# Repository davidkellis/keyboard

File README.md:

# TKL Low-Profile Bluetooth Keyboard (Project Notes)

## Decisions so far
- Layout: ANSI TKL (87-key).
- Switches: Kailh Deep Sea Silent Mini Low-Profile (Kailh page indicates Choc v2 family / PG1353).
- Footprint target: Choc v2 (not Cherry MX pin layout, not Choc v1 keycaps).
- Stem: MX-style "+" stem (per Choc v2 description).
- Hot-swap: required.
- Switch footprints: MX_V2 Kailh PG1353 hotswap library (Kailh_PG1353_Hotswap).
- Controller: nice!nano v2-compatible BLE clones (same pinout as nice!nano v2).
- Features: no rotary encoder, no OLED; white backlight via edge-lit plate.
- Case: custom, as thin as possible.
- Firmware: ZMK.
- Fn layer: right Menu key.
- Device switching: map Device 1/2/3 to the three keys right of F12 (Print/Scroll/Pause positions).
- Keymap change: Insert key performs Print Screen.
- Re-pair: Fn+Device 1/2/3 macros force-select profile 0/1/2, clear bond (BT_CLR), then re-select that profile to enter pairing; avoids BT_CLR_ALL. Order: BT_SEL N -> BT_CLR -> BT_SEL N.
- Device select: tap Device 1/2/3 selects and connects to profile 0/1/2.
- Battery: 4 mm thickness, JST-PH.
- Keycaps: low-profile, 8–9 mm height.
- Stabilizers: Kailh Choc low-profile plate-mount (4x 2u, 1x 6.25u).
- Backlight: single-zone white; use 1 mm clear plate as the edge-lit light guide with up to 16 side-emitting 1206 LEDs around the perimeter; warm/neutral based on LED availability.
- External power switch: yes, edge-mounted slide switch on the back edge (back-right).
- Reset/boot access: onboard only.
- Matrix: 8x16; rows on nice!nano (D4-D9, D16, D14) and columns on MCP23017.
- MCP23017 I2C address: 0x20 (A0-A2 tied to GND).
- PCB thickness: 1.2 mm (initial assumption for thin build).
- KiCad libraries: ScottoKicad vendored at kicad/lib/ScottoKicad.

## Findings / constraints
- Kailh product note: these switches are not compatible with Cherry MX key pin layouts and not compatible with Choc v1 keycaps.
- Beekeeb Choc v2 page: Choc v2 uses the same hot-swap sockets as Choc v1.
- Thin build drivers: battery thickness, PCB thickness, and component height will dominate overall thickness.

## Open decisions
- Warm vs neutral LED selection based on availability.
- LED part selection based on availability (side-emitting 1206, warm/neutral).
- Side-emitting LED footprint (current schematic uses generic 1206 placeholder).

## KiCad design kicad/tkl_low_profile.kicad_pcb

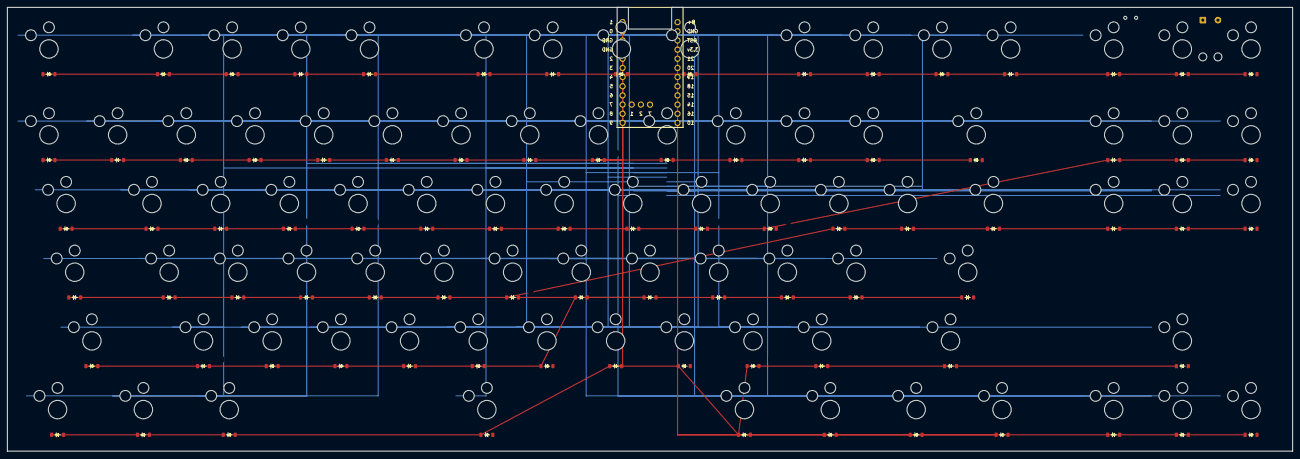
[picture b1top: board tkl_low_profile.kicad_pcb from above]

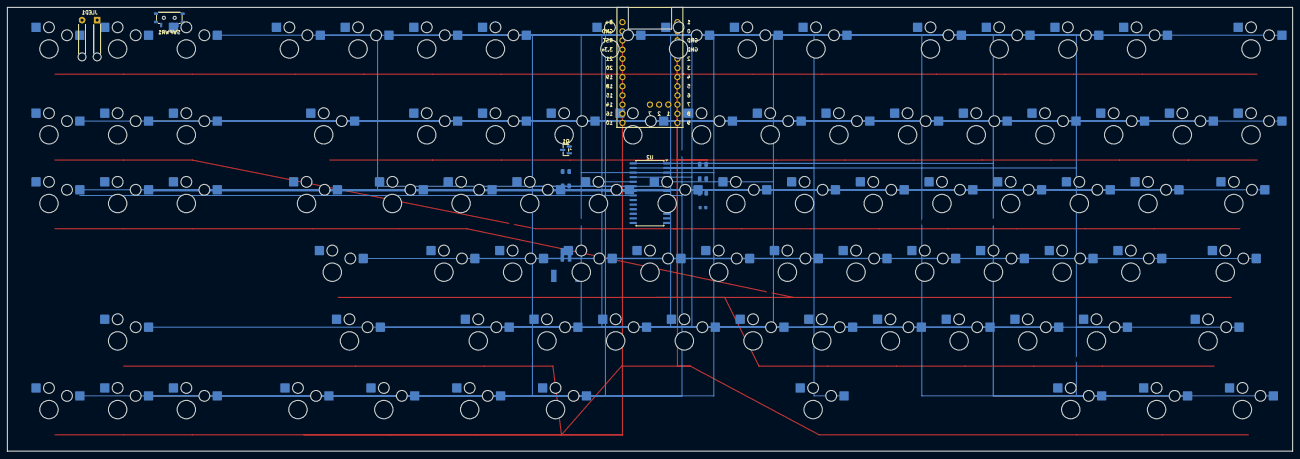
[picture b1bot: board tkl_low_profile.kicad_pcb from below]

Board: 2 copper layers, 356.4 x 123.1 mm, 186 parts (99 on the bottom side), 121 nets.

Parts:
C1: 0.1u; Capacitor_0603
D1, D2, D3, D4, D5, D6, D7, D8, D9, D10, D11, D12, D13, D14, D15, D16, D17, D18, D19, D20, D21, D22, D23, D24, D25, D26, D27, D28, D29, D30, D31, D32, D33, D34, D35, D36, D37, D38, D39, D40, D41, D42, D43, D44, D45, D46, D47, D48, D49, D50, D51, D52, D53, D54, D55, D56, D57, D58, D59, D60, D61, D62, D63, D64, D65, D66, D67, D68, D69, D70, D71, D72, D73, D74, D75, D76, D77, D78, D79, D80, D81, D82, D83, D84, D85, D86, D87: D; Diode_SOD-123
JBAT1: JST-PH; Connector_1x02_JST-PH
JLED1: LED_HARNESS; SolderWire-0.25sqmm_1x02_P4.2mm_D0.65mm_OD1.7mm_Relief
Q1: NMOS; SOT-23
R1, R2: 4.7k; Resistor_0805
R3: 10k; Resistor_0805
R4: 100; Resistor_0805
R5: 100k; Resistor_0805
SW1, SW2, SW3, SW4, SW5, SW6, SW7, SW8, SW9, SW10, SW11, SW12, SW13, SW14, SW15, SW16, SW17, SW18, SW19, SW20, SW21, SW22, SW23, SW24, SW25, SW26, SW27, SW28, SW29, SW31, SW32, SW33, SW35, SW36, SW37, SW38, SW39, SW40, SW41, SW42, SW43, SW44, SW45, SW46, SW48, SW49, SW50, SW52, SW53, SW54, SW55, SW56, SW57, SW58, SW59, SW60, SW61, SW62, SW65, SW66, SW67, SW68, SW69, SW70, SW71, SW72, SW73, SW74, SW76, SW85, SW86, SW87: SW_Push; Kailh-PG1353-Hotswap-1U
SW30: SW_Push; Kailh-PG1353-Hotswap-2U
SW34, SW47: SW_Push; Kailh-PG1353-Hotswap-1.5U
SW51: SW_Push; Kailh-PG1353-Hotswap-1.75U
SW63, SW64: SW_Push; Kailh-PG1353-Hotswap-2.25U
SW75: SW_Push; Kailh-PG1353-Hotswap-2.75U
SW77, SW78, SW79, SW81, SW82, SW83, SW84: SW_Push; Kailh-PG1353-Hotswap-1.25U
SW80: SW_Push; Kailh-PG1353-Hotswap-6.25U
SWPWR1: Power_Switch; Switch_MSK12C02
U1: Nice_Nano_V2
U2: MCP23017; SOIC-28W_7.5x17.9mm_P1.27mm

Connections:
/+3V3: C1.2, JLED1.1, R1.2, R2.2, R3.2, U1.16 (15), U2.10 (VSS)
/BL_GATE: Q1.1 (G), R4.1, R5.1
/BL_NEG: JLED1.2, Q1.2 (S)
/BL_PWM: R4.2, U1.24 (B+)
/GND: C1.1, Q1.3 (D), R5.2, U1.9 (6), U1.10 (7), U1.14 (16), U2.9 (VDD), U2.12 (SCK), U2.13 (SDA)
/MCP_RESET: R3.1, U2.20 (INTA)
/SCL: R2.1, U1.7 (4), U2.16 (A1)
/SDA: R1.1, U1.8 (5), U2.15 (A0)
/VBAT: SWPWR1.2 (B), U1.13 (10)
/VBAT_RAW: JBAT1.1, SWPWR1.3 (C)
COL0: SW1.1, SW17.1, SW31.1, SW45.1, SW58.1, SW71.1, SW82.1, SW85.1, U2.8 (GPB7)
COL1: SW2.1, SW18.1, SW32.1, SW46.1, SW59.1, SW72.1, SW83.1, SW86.1, U2.7 (GPB6)
COL2: SW3.1, SW19.1, SW33.1, SW47.1, SW60.1, SW73.1, SW84.1, SW87.1, U2.6 (GPB5)
COL3: SW4.1, SW20.1, SW34.1, SW48.1, SW61.1, SW74.1, U2.5 (GPB4)
COL4: SW5.1, SW21.1, SW35.1, SW49.1, SW62.1, SW75.1, U2.4 (GPB3)
COL5: SW6.1, SW22.1, SW36.1, SW50.1, SW63.1, SW76.1, U2.3 (GPB2)
COL6: SW7.1, SW23.1, SW37.1, SW51.1, SW64.1, SW77.1, U2.2 (GPB1)
COL7: SW8.1, SW24.1, SW38.1, SW52.1, SW65.1, SW78.1, U2.1 (GPB0)
COL8: SW9.1, SW25.1, SW39.1, SW53.1, SW66.1, SW79.1, U2.28 (GPA7)
COL9: SW10.1, SW26.1, SW40.1, SW54.1, SW67.1, SW80.1, U2.27 (GPA6)
COL10: SW11.1, SW27.1, SW41.1, SW55.1, SW68.1, SW81.1, U2.26 (GPA5)
COL11: SW12.1, SW28.1, SW42.1, SW56.1, SW69.1, U2.25 (GPA4)
COL12: SW13.1, SW29.1, SW43.1, SW57.1, SW70.1, U2.24 (GPA3)
COL13: SW14.1, SW30.1, SW44.1, U2.23 (GPA2)
COL14: SW15.1, U2.22 (GPA1)
COL15: SW16.1, U2.21 (GPA0)
unnamed: D1.2 (A), SW1.2
unnamed: D2.2 (A), SW2.2
unnamed: D3.2 (A), SW3.2
unnamed: D4.2 (A), SW4.2
unnamed: D5.2 (A), SW5.2
unnamed: D6.2 (A), SW6.2
unnamed: D7.2 (A), SW7.2
unnamed: D8.2 (A), SW8.2
unnamed: D9.2 (A), SW9.2
unnamed: D10.2 (A), SW10.2
unnamed: D11.2 (A), SW11.2
unnamed: D12.2 (A), SW12.2
unnamed: D13.2 (A), SW13.2
unnamed: D14.2 (A), SW14.2
unnamed: D15.2 (A), SW15.2
unnamed: D16.2 (A), SW16.2
unnamed: D17.2 (A), SW17.2
unnamed: D18.2 (A), SW18.2
unnamed: D19.2 (A), SW19.2
unnamed: D20.2 (A), SW20.2
unnamed: D21.2 (A), SW21.2
unnamed: D22.2 (A), SW22.2
unnamed: D23.2 (A), SW23.2
unnamed: D24.2 (A), SW24.2
unnamed: D25.2 (A), SW25.2
unnamed: D26.2 (A), SW26.2
unnamed: D27.2 (A), SW27.2
unnamed: D28.2 (A), SW28.2
unnamed: D29.2 (A), SW29.2
unnamed: D30.2 (A), SW30.2
unnamed: D31.2 (A), SW31.2
unnamed: D32.2 (A), SW32.2
unnamed: D33.2 (A), SW33.2
unnamed: D34.2 (A), SW34.2
unnamed: D35.2 (A), SW35.2
unnamed: D36.2 (A), SW36.2
unnamed: D37.2 (A), SW37.2
unnamed: D38.2 (A), SW38.2
unnamed: D39.2 (A), SW39.2
unnamed: D40.2 (A), SW40.2
unnamed: D41.2 (A), SW41.2
unnamed: D42.2 (A), SW42.2
unnamed: D43.2 (A), SW43.2
unnamed: D44.2 (A), SW44.2
unnamed: D45.2 (A), SW45.2
unnamed: D46.2 (A), SW46.2
unnamed: D47.2 (A), SW47.2
unnamed: D48.2 (A), SW48.2
unnamed: D49.2 (A), SW49.2
unnamed: D50.2 (A), SW50.2
unnamed: D51.2 (A), SW51.2
unnamed: D52.2 (A), SW52.2
unnamed: D53.2 (A), SW53.2
unnamed: D54.2 (A), SW54.2
unnamed: D55.2 (A), SW55.2
unnamed: D56.2 (A), SW56.2
unnamed: D57.2 (A), SW57.2
unnamed: D58.2 (A), SW58.2
unnamed: D59.2 (A), SW59.2
unnamed: D60.2 (A), SW60.2
unnamed: D61.2 (A), SW61.2
unnamed: D62.2 (A), SW62.2
unnamed: D63.2 (A), SW63.2
unnamed: D64.2 (A), SW64.2
unnamed: D65.2 (A), SW65.2
unnamed: D66.2 (A), SW66.2
unnamed: D67.2 (A), SW67.2
unnamed: D68.2 (A), SW68.2
unnamed: D69.2 (A), SW69.2
unnamed: D70.2 (A), SW70.2
unnamed: D71.2 (A), SW71.2
unnamed: D72.2 (A), SW72.2
unnamed: D73.2 (A), SW73.2
unnamed: D74.2 (A), SW74.2
unnamed: D75.2 (A), SW75.2
unnamed: D76.2 (A), SW76.2
unnamed: D77.2 (A), SW77.2
unnamed: D78.2 (A), SW78.2
unnamed: D79.2 (A), SW79.2
unnamed: D80.2 (A), SW80.2
unnamed: D81.2 (A), SW81.2
unnamed: D82.2 (A), SW82.2
unnamed: D83.2 (A), SW83.2
unnamed: D84.2 (A), SW84.2
unnamed: D85.2 (A), SW85.2
unnamed: D86.2 (A), SW86.2
unnamed: D87.2 (A), SW87.2
ROW0: D1.1 (K), D2.1 (K), D3.1 (K), D4.1 (K), D5.1 (K), D6.1 (K), D7.1 (K), D8.1 (K), D9.1 (K), D10.1 (K), D11.1 (K), D12.1 (K), D13.1 (K), D14.1 (K), D15.1 (K), D16.1 (K), U1.6 (3)
ROW1: D17.1 (K), D18.1 (K), D19.1 (K), D20.1 (K), D21.1 (K), D22.1 (K), D23.1 (K), D24.1 (K), D25.1 (K), D26.1 (K), D27.1 (K), D28.1 (K), D29.1 (K), D30.1 (K), U1.5 (2)
ROW2: D31.1 (K), D32.1 (K), D33.1 (K), D34.1 (K), D35.1 (K), D36.1 (K), D37.1 (K), D38.1 (K), D39.1 (K), D40.1 (K), D41.1 (K), D42.1 (K), D43.1 (K), D44.1 (K), U1.4 (GND)
ROW3: D45.1 (K), D46.1 (K), D47.1 (K), D48.1 (K), D49.1 (K), D50.1 (K), D51.1 (K), D52.1 (K), D53.1 (K), D54.1 (K), D55.1 (K), D56.1 (K), D57.1 (K), U1.3 (GND)
ROW4: D58.1 (K), D59.1 (K), D60.1 (K), D61.1 (K), D62.1 (K), D63.1 (K), D64.1 (K), D65.1 (K), D66.1 (K), D67.1 (K), D68.1 (K), D69.1 (K), D70.1 (K), U1.2 (0)
ROW5: D71.1 (K), D72.1 (K), D73.1 (K), D74.1 (K), D75.1 (K), D76.1 (K), D77.1 (K), D78.1 (K), D79.1 (K), D80.1 (K), D81.1 (K), U1.1
ROW6: D82.1 (K), D83.1 (K), D84.1 (K), U1.23 (GND)
ROW7: D85.1 (K), D86.1 (K), D87.1 (K), U1.22 (RST)

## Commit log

2025-12-27 created the plan for the keyboard
2025-12-27 finalized plan
